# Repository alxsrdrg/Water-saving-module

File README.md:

# Water-saving-module
This is the data gatherer for a bigger project that will collect ambient data to save water while watering plants.
Hello, my name is Alexis. I am part of ACOIIN in Chile, and I designed this PCB to save water during the process of watering plants.

Most people don’t know how much water plants actually need to be watered efficiently, so I designed this small ATtiny85-based data gatherer to interface with other modules that will help water plants more efficiently—saving water, saving money, and helping the environment.

To use it you must upload the code to an ATtiny85 connect it to the pcb then upload the recivers code to an arduino with the reciver and watch the serial interface for the data this will be feeded into a algorthm tha will take the best moment for you to water the plants (WIP)

(BOM: https://docs.google.com/spreadsheets/d/1GQ0v_dI7ZX-GIWkH-TXZdrfXvmL1TNvHDqjCibz4H14/edit?usp=sharing)

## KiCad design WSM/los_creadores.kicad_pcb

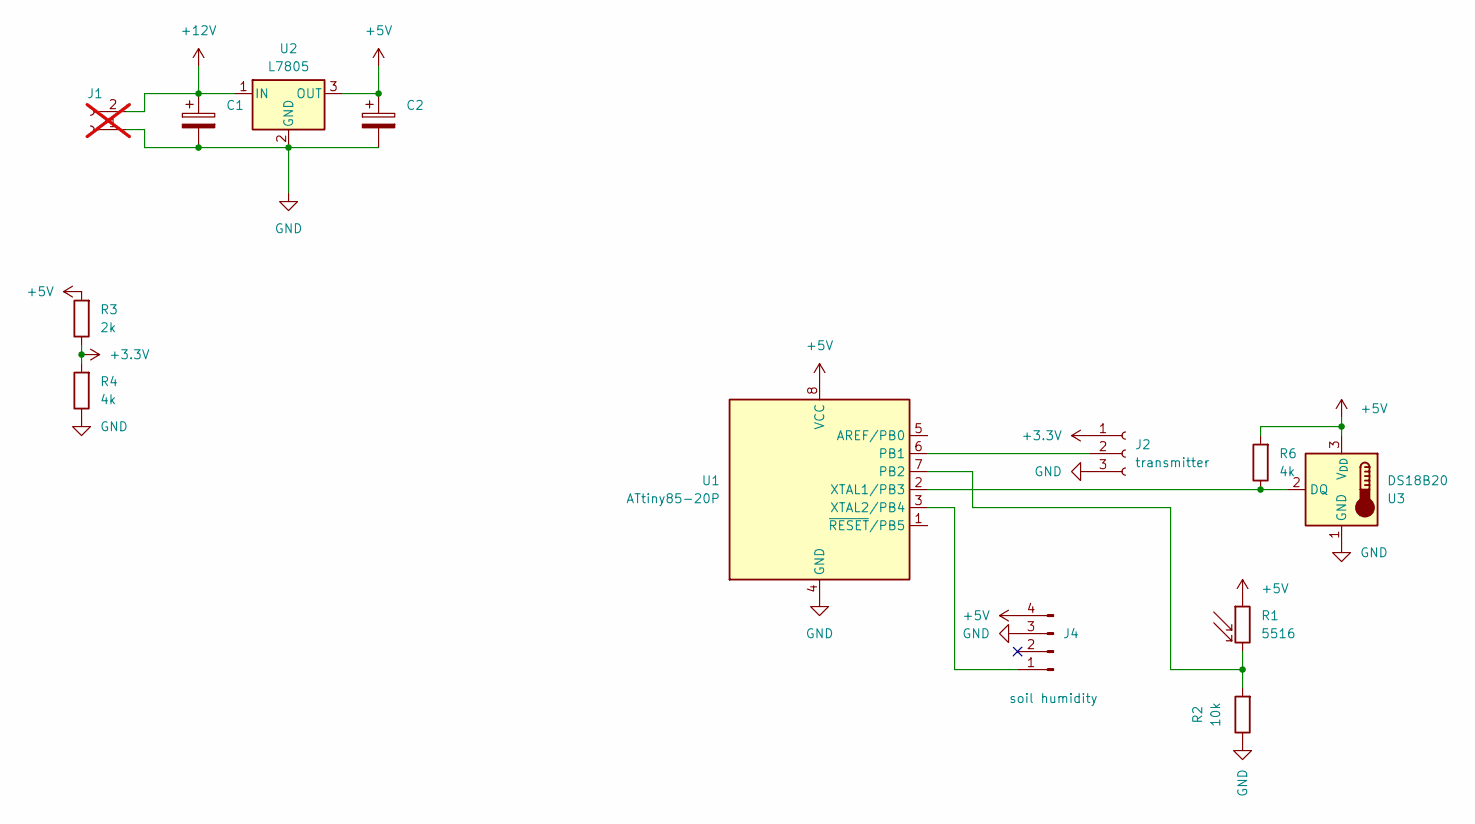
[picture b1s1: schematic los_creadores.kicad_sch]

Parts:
C1, C2: C_Polarized; CP_Radial_D4.0mm_P1.50mm
J1: Conn_01x02_Socket; PinHeader_1x02_P2.00mm_Vertical; not fitted
J2: transmitter; PinHeader_1x03_P2.00mm_Vertical
J4: soil humidity; PinHeader_1x04_P2.00mm_Vertical
R1: 5516; R_LDR_5.0x4.1mm_P3mm_Vertical
R2: 10k; R_Axial_DIN0207_L6.3mm_D2.5mm_P5.08mm_Vertical
R3: 2k; R_Axial_DIN0207_L6.3mm_D2.5mm_P5.08mm_Vertical
R4, R6: 4k; R_Axial_DIN0207_L6.3mm_D2.5mm_P5.08mm_Vertical
U1: ATtiny85-20P; DIP-8_W7.62mm
U2: L7805; TO-220-3_Horizontal_TabDown
U3: DS18B20; TO-92_Inline

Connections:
+3.3V: J2.1, R3.1, R4.2
+5V: C2.1, J4.4, R1.1, R3.2, R6.2, U1.8 (VCC), U2.3 (OUT), U3.3 (V_{DD})
+12V: C1.1, J1.2, U2.1 (IN)
GND: C1.2, C2.2, J1.1, J2.3, J4.3, R2.1, R4.1, U1.4 (GND), U2.2 (GND), U3.1 (GND)
unnamed: J2.2, U1.6 (PB1)
unnamed: J4.1, U1.3 (XTAL2/PB4)
unnamed: R1.2, R2.2, U1.7 (PB2)
unnamed: R6.1, U1.2 (XTAL1/PB3), U3.2 (DQ)

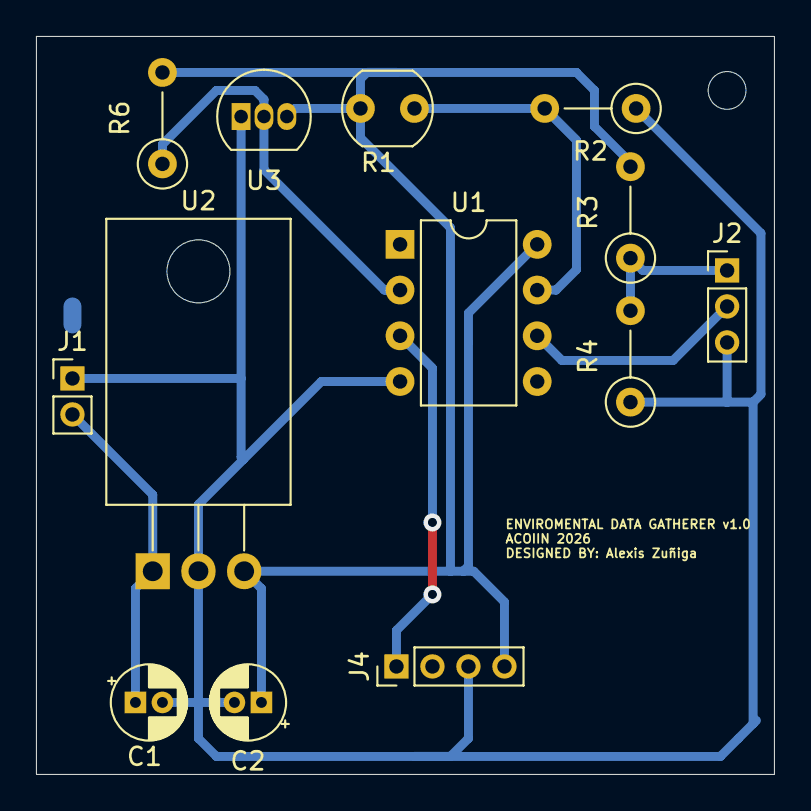
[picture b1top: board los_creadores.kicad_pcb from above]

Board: 2 copper layers, 41.0 x 41.0 mm, 13 parts (0 on the bottom side), 8 nets.

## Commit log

2026-03-10 Enhance README with project and designer details
    Added introduction about the designer and project goals.
2026-03-10 Add image to README for visualization
    Added an image to the README for better visualization.
